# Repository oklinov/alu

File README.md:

View this project on [CADLAB.io](https://cadlab.io/project//TODO). 

# Template for PB170 projects at FI MU Brno
Add your user guide here.

## Photos

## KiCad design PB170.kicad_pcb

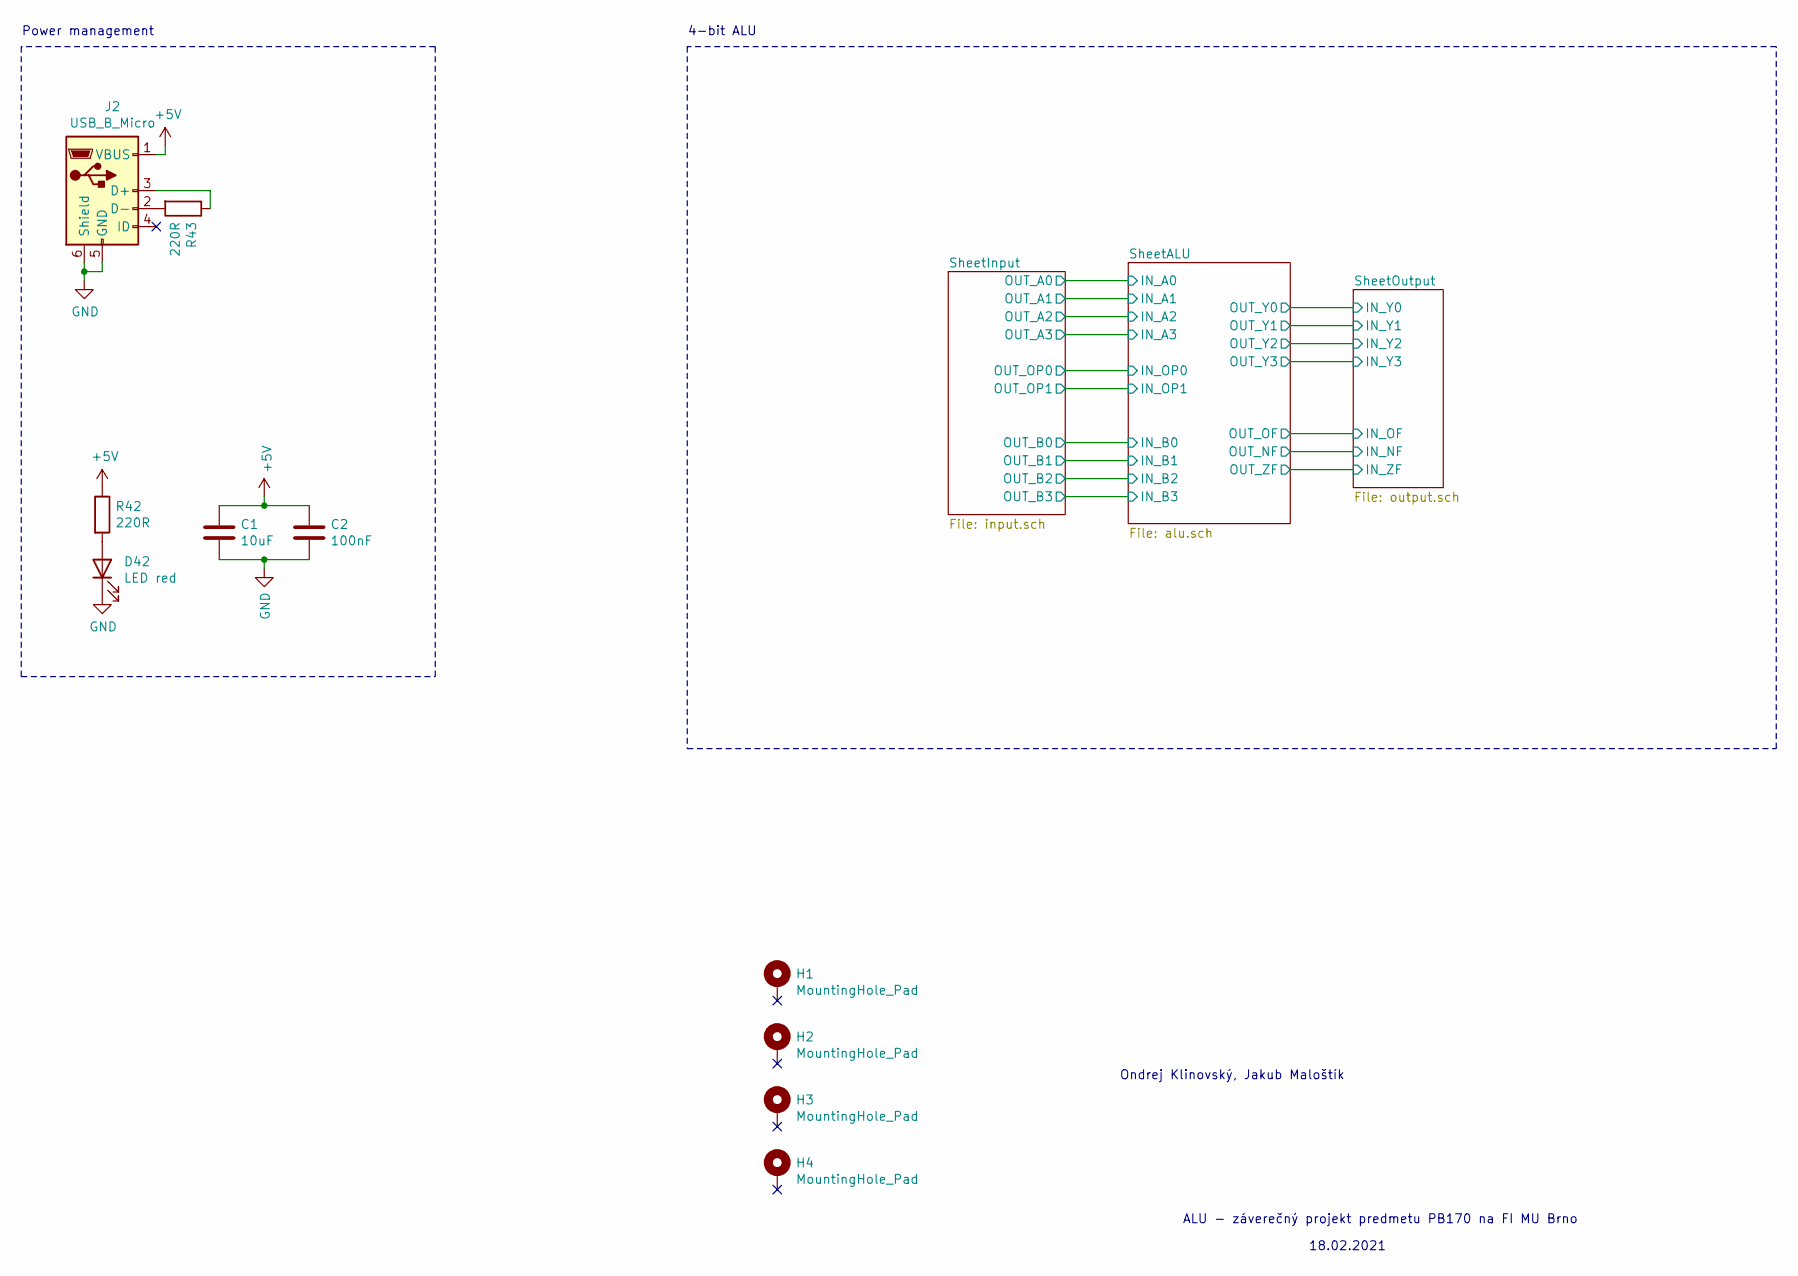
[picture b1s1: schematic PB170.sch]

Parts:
C1: 10uF; C_0805_2012Metric; LCSC C15850
C2: 100nF; C_0805_2012Metric; LCSC C14663
D42: LED red; LED_0603_1608Metric; LCSC C2286
H1, H2, H3, H4: MountingHole_Pad; MountingHole_3.2mm_M3_Pad
J2: USB_B_Micro; MICRO-USB-SMD_MICROXNJ; LCSC C404969
R42, R43: 220R; R_0603_1608Metric; LCSC C22962

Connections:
+5V: C1.1, C2.1, J2.1 (VBUS), R42.1; also elsewhere on the board
GND: C1.2, C2.2, D42.1 (K), J2.5 (GND), J2.6 (Shield); also elsewhere on the board
unnamed: D42.2 (A), R42.2
unnamed: J2.2 (D-), R43.2
unnamed: J2.3 (D+), R43.1

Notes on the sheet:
ALU - záverečný projekt predmetu PB170 na FI MU Brno
Ondrej Klinovský, Jakub Maloštík
Power management
4-bit ALU
18.02.2021

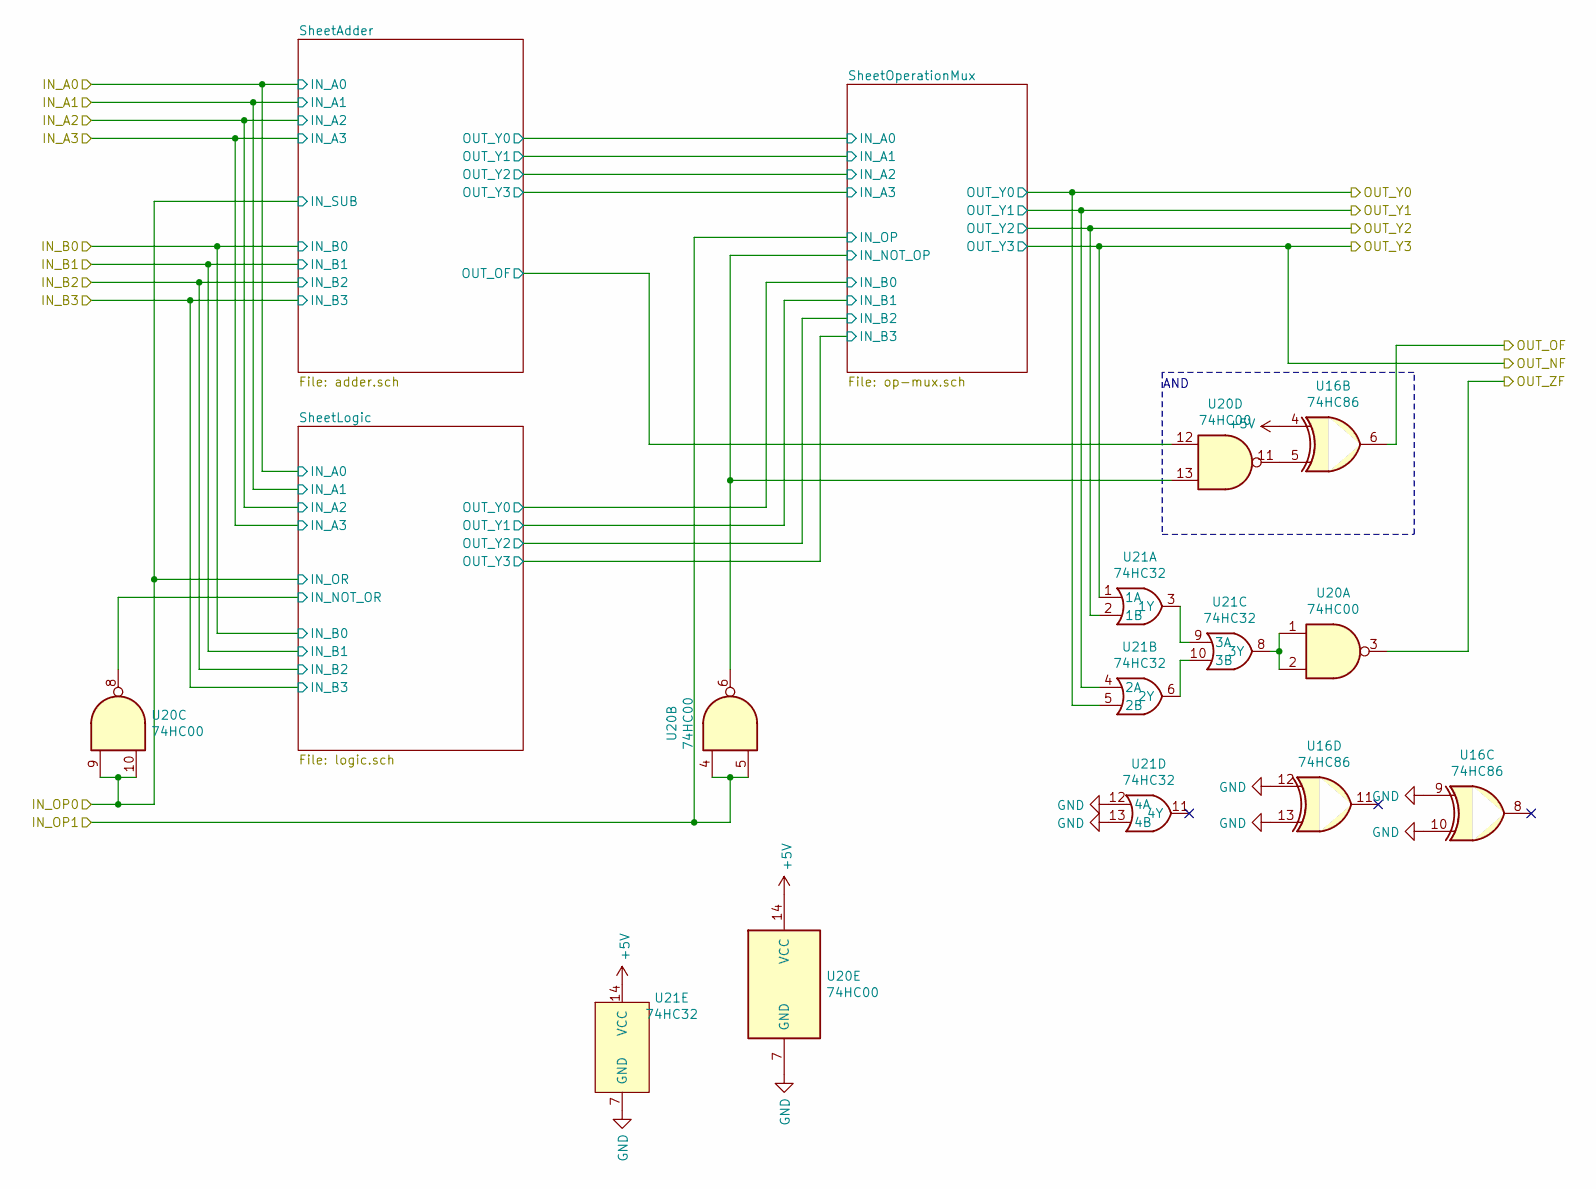
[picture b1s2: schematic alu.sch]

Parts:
U16: 74HC86; TSSOP-14_4.4x5mm_P0.65mm; LCSC C117522
U20: 74HC00; TSSOP-14_4.4x5mm_P0.65mm; LCSC C6807
U21: 74HC32; SOIC-14_3.9x8.7mm_P1.27mm; LCSC C5632

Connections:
+5V: U16.4, U20.14 (VCC), U21.14 (VCC); also elsewhere on the board
/SheetALU/IN_OP0: U20.9, U20.10; also elsewhere on the board
/SheetALU/IN_OP1: U20.4, U20.5; also elsewhere on the board
/SheetALU/SheetAdder/OUT_OF: U20.12; also elsewhere on the board
/SheetALU/SheetLogic/IN_NOT_OR: U20.8; also elsewhere on the board
/SheetALU/SheetOperationMux/IN_NOT_OP: U20.6, U20.13; also elsewhere on the board
/SheetOutput/IN_NF: U21.1 (1A); also elsewhere on the board
/SheetOutput/IN_OF: U16.6; also elsewhere on the board
/SheetOutput/IN_Y0: U21.5 (2B); also elsewhere on the board
/SheetOutput/IN_Y1: U21.4 (2A); also elsewhere on the board
/SheetOutput/IN_Y2: U21.2 (1B); also elsewhere on the board
/SheetOutput/IN_ZF: U20.3; also elsewhere on the board
GND: U16.9, U16.10, U16.12, U16.13, U20.7 (GND), U21.7 (GND), U21.12 (4A), U21.13 (4B); also elsewhere on the board
unnamed: U16.5, U20.11
unnamed: U20.1, U20.2, U21.8 (3Y)
unnamed: U21.3 (1Y), U21.9 (3A)
unnamed: U21.6 (2Y), U21.10 (3B)

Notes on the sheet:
AND

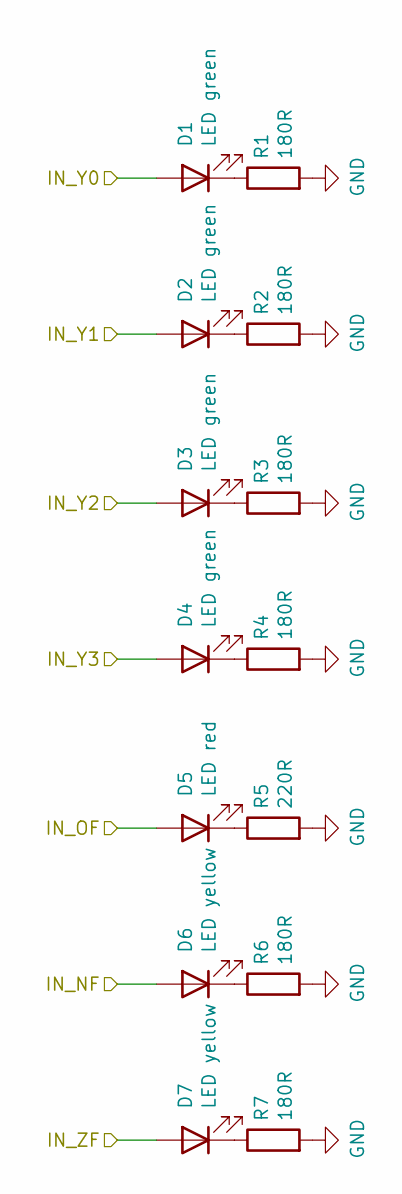
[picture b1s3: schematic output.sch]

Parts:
D1, D2, D3, D4: LED green; LED_0603_1608Metric; LCSC C72043
D5: LED red; LED_0603_1608Metric; LCSC C2286
D6, D7: LED yellow; LED_0603_1608Metric; LCSC C72038
R1, R2, R3, R4, R6, R7: 180R; R_0603_1608Metric; LCSC C22828
R5: 220R; R_0603_1608Metric; LCSC C22962

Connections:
/SheetOutput/IN_NF: D4.2 (A), D6.2 (A); also elsewhere on the board
/SheetOutput/IN_OF: D5.2 (A); also elsewhere on the board
/SheetOutput/IN_Y0: D1.2 (A); also elsewhere on the board
/SheetOutput/IN_Y1: D2.2 (A); also elsewhere on the board
/SheetOutput/IN_Y2: D3.2 (A); also elsewhere on the board
/SheetOutput/IN_ZF: D7.2 (A); also elsewhere on the board
GND: R1.2, R2.2, R3.2, R4.2, R5.2, R6.2, R7.2; also elsewhere on the board
unnamed: D1.1 (K), R1.1
unnamed: D2.1 (K), R2.1
unnamed: D3.1 (K), R3.1
unnamed: D4.1 (K), R4.1
unnamed: D5.1 (K), R5.1
unnamed: D6.1 (K), R6.1
unnamed: D7.1 (K), R7.1

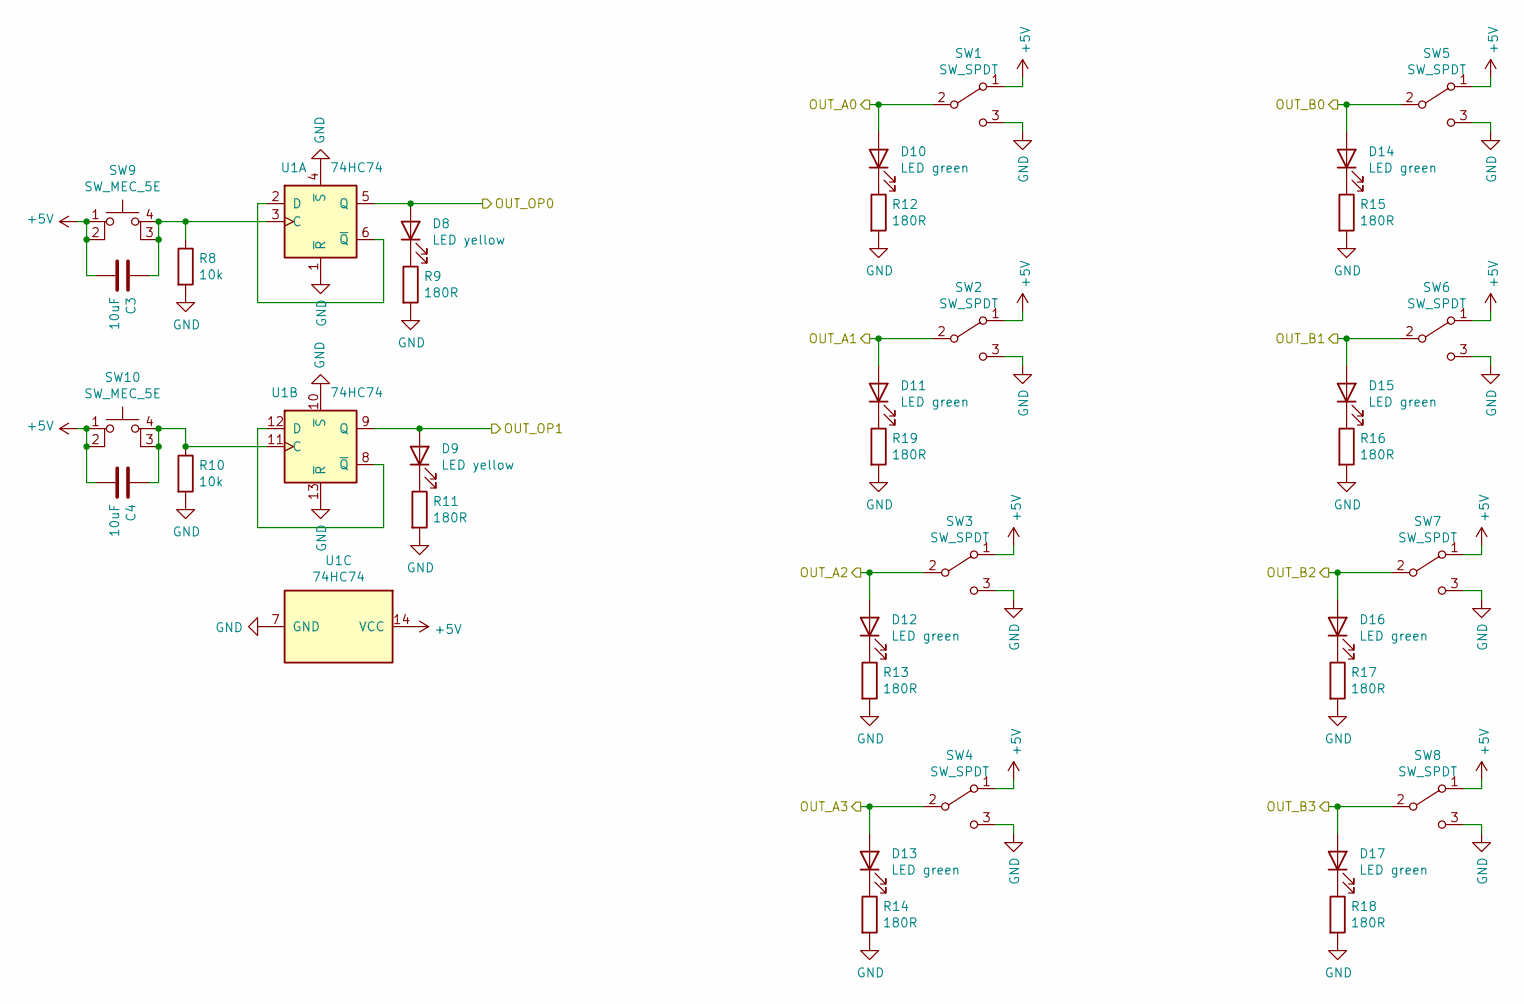
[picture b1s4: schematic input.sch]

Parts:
C3, C4: 10uF; C_0805_2012Metric; LCSC C15850
D8, D9: LED yellow; LED_0603_1608Metric; LCSC C72038
D10, D11, D12, D13, D14, D15, D16, D17: LED green; LED_0603_1608Metric; LCSC C72043
R8, R10: 10k; R_0603_1608Metric; LCSC C25804
R9, R11, R12, R13, R14, R15, R16, R17, R18, R19: 180R; R_0603_1608Metric; LCSC C22828
SW1, SW2, SW3, SW4, SW5, SW6, SW7, SW8: SW_SPDT; toggleSwitch; LCSC C136718
SW9, SW10: SW_MEC_5E; TactileSwitch_C381064; LCSC C381064
U1: 74HC74; TSSOP-14_4.4x5mm_P0.65mm; LCSC C6761

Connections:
+5V: C3.2, C4.2, SW1.1 (A), SW2.1 (A), SW3.1 (A), SW4.1 (A), SW5.1 (A), SW6.1 (A), SW7.1 (A), SW8.1 (A), SW9.1, SW9.2, SW10.1, SW10.2, U1.14 (VCC); also elsewhere on the board
/SheetALU/IN_A0: D10.2 (A), SW1.2 (B); also elsewhere on the board
/SheetALU/IN_A1: D11.2 (A), SW2.2 (B); also elsewhere on the board
/SheetALU/IN_A2: D12.2 (A), SW3.2 (B); also elsewhere on the board
/SheetALU/IN_A3: D13.2 (A), SW4.2 (B); also elsewhere on the board
/SheetALU/IN_B0: D14.2 (A), SW5.2 (B); also elsewhere on the board
/SheetALU/IN_B1: D15.2 (A), SW6.2 (B); also elsewhere on the board
/SheetALU/IN_B2: D16.2 (A), SW7.2 (B); also elsewhere on the board
/SheetALU/IN_B3: D17.2 (A), SW8.2 (B); also elsewhere on the board
/SheetALU/IN_OP0: D8.2 (A), U1.5 (Q); also elsewhere on the board
/SheetALU/IN_OP1: D9.2 (A), U1.9 (Q); also elsewhere on the board
GND: R8.2, R9.2, R10.2, R11.2, R12.2, R13.2, R14.2, R15.2, R16.2, R17.2, R18.2, R19.2, SW1.3 (C), SW2.3 (C), SW3.3 (C), SW4.3 (C), SW5.3 (C), SW6.3 (C), SW7.3 (C), SW8.3 (C), U1.1 (~R), U1.4 (~S), U1.7 (GND), U1.10 (~S), U1.13 (~R); also elsewhere on the board
unnamed: C3.1, R8.1, SW9.3 (K), SW9.4 (A), U1.3 (C)
unnamed: C4.1, R10.1, SW10.3 (K), SW10.4 (A), U1.11 (C)
unnamed: D8.1 (K), R9.1
unnamed: D9.1 (K), R11.1
unnamed: D10.1 (K), R12.1
unnamed: D11.1 (K), R19.1
unnamed: D12.1 (K), R13.1
unnamed: D13.1 (K), R14.1
unnamed: D14.1 (K), R15.1
unnamed: D15.1 (K), R16.1
unnamed: D16.1 (K), R17.1
unnamed: D17.1 (K), R18.1
unnamed: U1.2 (D), U1.6 (~Q)
unnamed: U1.8 (~Q), U1.12 (D)

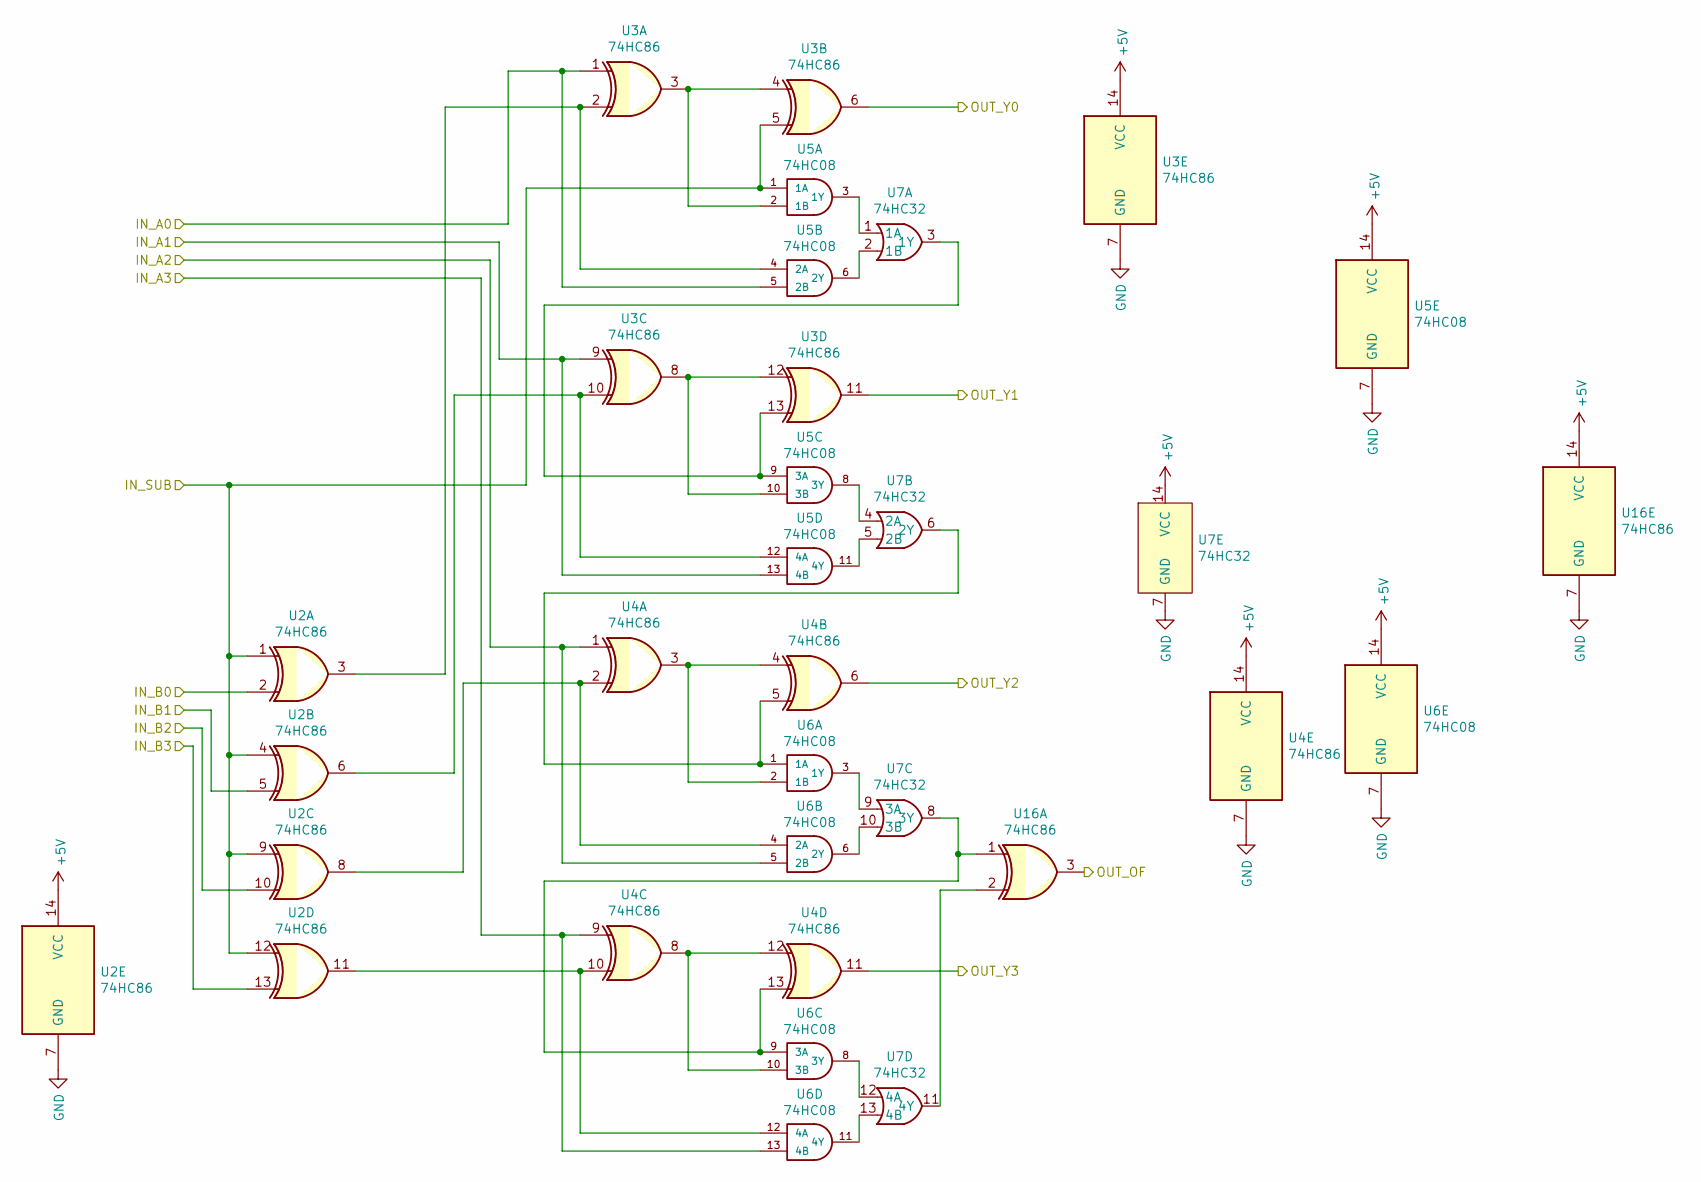
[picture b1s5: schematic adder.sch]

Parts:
U2, U3, U4, U16: 74HC86; TSSOP-14_4.4x5mm_P0.65mm; LCSC C117522
U5, U6: 74HC08; SOIC-14_3.9x8.7mm_P1.27mm; LCSC C5593
U7: 74HC32; SOIC-14_3.9x8.7mm_P1.27mm; LCSC C5632

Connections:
+5V: U2.14 (VCC), U3.14 (VCC), U4.14 (VCC), U5.14 (VCC), U6.14 (VCC), U7.14 (VCC), U16.14 (VCC); also elsewhere on the board
/SheetALU/IN_A0: U3.1, U5.5 (2B); also elsewhere on the board
/SheetALU/IN_A1: U3.9, U5.13 (4B); also elsewhere on the board
/SheetALU/IN_A2: U4.1, U6.5 (2B); also elsewhere on the board
/SheetALU/IN_A3: U4.9, U6.13 (4B); also elsewhere on the board
/SheetALU/IN_B0: U2.2; also elsewhere on the board
/SheetALU/IN_B1: U2.5; also elsewhere on the board
/SheetALU/IN_B2: U2.10; also elsewhere on the board
/SheetALU/IN_B3: U2.13; also elsewhere on the board
/SheetALU/IN_OP0: U2.1, U2.4, U2.9, U2.12, U3.5, U5.1 (1A); also elsewhere on the board
/SheetALU/SheetAdder/OUT_OF: U16.3; also elsewhere on the board
/SheetALU/SheetOperationMux/IN_A0: U3.6; also elsewhere on the board
/SheetALU/SheetOperationMux/IN_A1: U3.11; also elsewhere on the board
/SheetALU/SheetOperationMux/IN_A2: U4.6; also elsewhere on the board
/SheetALU/SheetOperationMux/IN_A3: U4.11; also elsewhere on the board
GND: U2.7 (GND), U3.7 (GND), U4.7 (GND), U5.7 (GND), U6.7 (GND), U7.7 (GND), U16.7 (GND); also elsewhere on the board
unnamed: U2.3, U3.2, U5.4 (2A)
unnamed: U2.6, U3.10, U5.12 (4A)
unnamed: U2.8, U4.2, U6.4 (2A)
unnamed: U2.11, U4.10, U6.12 (4A)
unnamed: U3.3, U3.4, U5.2 (1B)
unnamed: U3.8, U3.12, U5.10 (3B)
unnamed: U3.13, U5.9 (3A), U7.3 (1Y)
unnamed: U4.3, U4.4, U6.2 (1B)
unnamed: U4.5, U6.1 (1A), U7.6 (2Y)
unnamed: U4.8, U4.12, U6.10 (3B)
unnamed: U5.3 (1Y), U7.1 (1A)
unnamed: U5.6 (2Y), U7.2 (1B)
unnamed: U5.8 (3Y), U7.4 (2A)
unnamed: U5.11 (4Y), U7.5 (2B)
unnamed: U6.3 (1Y), U7.9 (3A)
unnamed: U6.6 (2Y), U7.10 (3B)
unnamed: U6.8 (3Y), U7.12 (4A)
unnamed: U6.11 (4Y), U7.13 (4B)
unnamed: U4.13, U6.9 (3A), U7.8 (3Y), U16.1
unnamed: U7.11 (4Y), U16.2

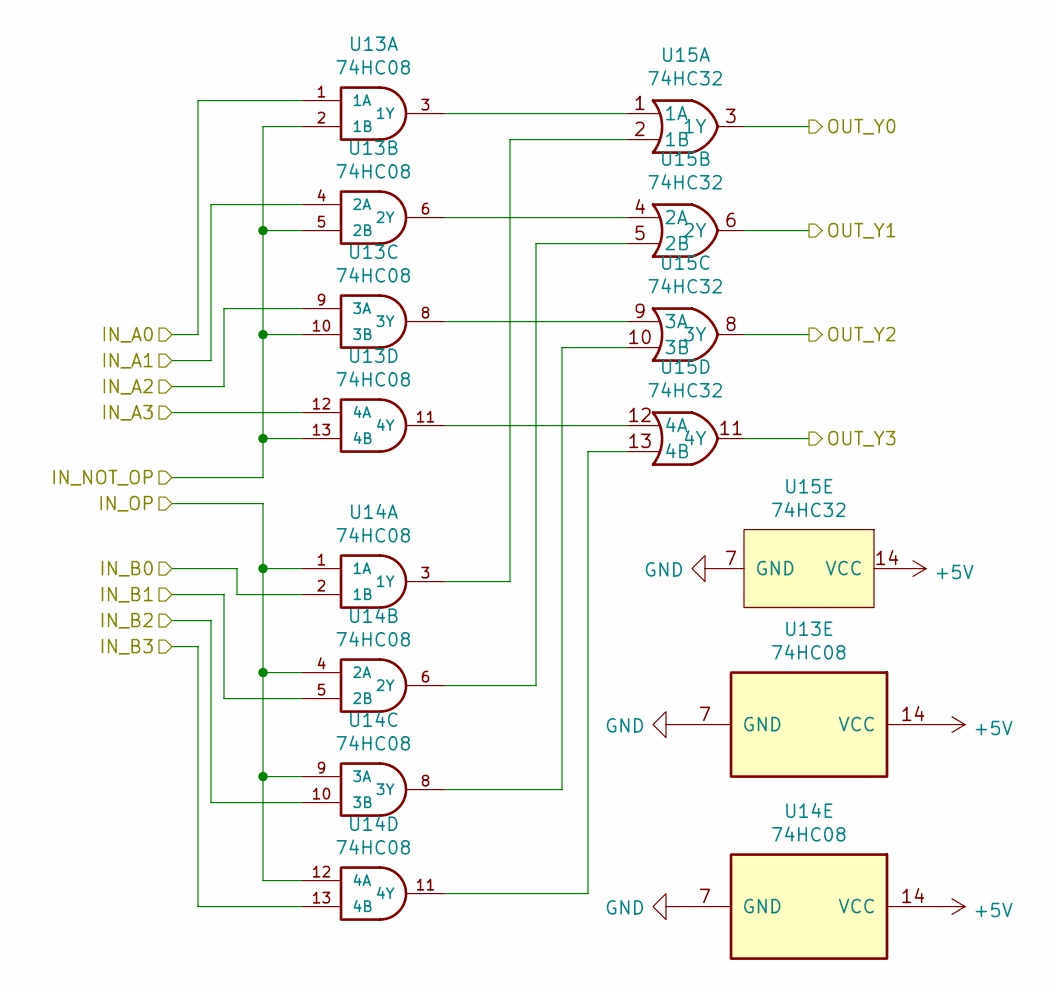
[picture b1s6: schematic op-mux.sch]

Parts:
U13, U14: 74HC08; SOIC-14_3.9x8.7mm_P1.27mm; LCSC C5593
U15: 74HC32; SOIC-14_3.9x8.7mm_P1.27mm; LCSC C5632

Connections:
+5V: U13.14 (VCC), U14.14 (VCC), U15.14 (VCC); also elsewhere on the board
/SheetALU/IN_OP1: U14.1 (1A), U14.4 (2A), U14.9 (3A), U14.12 (4A); also elsewhere on the board
/SheetALU/SheetOperationMux/IN_A0: U13.1 (1A); also elsewhere on the board
/SheetALU/SheetOperationMux/IN_A1: U13.4 (2A); also elsewhere on the board
/SheetALU/SheetOperationMux/IN_A2: U13.9 (3A); also elsewhere on the board
/SheetALU/SheetOperationMux/IN_A3: U13.12 (4A); also elsewhere on the board
/SheetALU/SheetOperationMux/IN_B0: U14.2 (1B); also elsewhere on the board
/SheetALU/SheetOperationMux/IN_B1: U14.5 (2B); also elsewhere on the board
/SheetALU/SheetOperationMux/IN_B2: U14.10 (3B); also elsewhere on the board
/SheetALU/SheetOperationMux/IN_B3: U14.13 (4B); also elsewhere on the board
/SheetALU/SheetOperationMux/IN_NOT_OP: U13.2 (1B), U13.5 (2B), U13.10 (3B), U13.13 (4B); also elsewhere on the board
/SheetOutput/IN_NF: U15.11 (4Y); also elsewhere on the board
/SheetOutput/IN_Y0: U15.3 (1Y); also elsewhere on the board
/SheetOutput/IN_Y1: U15.6 (2Y); also elsewhere on the board
/SheetOutput/IN_Y2: U15.8 (3Y); also elsewhere on the board
GND: U13.7 (GND), U14.7 (GND), U15.7 (GND); also elsewhere on the board
unnamed: U13.3 (1Y), U15.1 (1A)
unnamed: U13.6 (2Y), U15.4 (2A)
unnamed: U13.8 (3Y), U15.9 (3A)
unnamed: U13.11 (4Y), U15.12 (4A)
unnamed: U14.3 (1Y), U15.2 (1B)
unnamed: U14.6 (2Y), U15.5 (2B)
unnamed: U14.8 (3Y), U15.10 (3B)
unnamed: U14.11 (4Y), U15.13 (4B)

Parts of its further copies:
U10, U11: 74HC08; SOIC-14_3.9x8.7mm_P1.27mm; LCSC C5593
U12: 74HC32; SOIC-14_3.9x8.7mm_P1.27mm; LCSC C5632

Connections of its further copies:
+5V: U10.14 (VCC), U11.14 (VCC), U12.14 (VCC); also elsewhere on the board
/SheetALU/IN_OP0: U11.1 (1A), U11.4 (2A), U11.9 (3A), U11.12 (4A); also elsewhere on the board
/SheetALU/SheetLogic/IN_NOT_OR: U10.2 (1B), U10.5 (2B), U10.10 (3B), U10.13 (4B); also elsewhere on the board
/SheetALU/SheetLogic/sheet6027A5E8/IN_A0: U10.1 (1A); also elsewhere on the board
/SheetALU/SheetLogic/sheet6027A5E8/IN_A1: U10.4 (2A); also elsewhere on the board
/SheetALU/SheetLogic/sheet6027A5E8/IN_A2: U10.9 (3A); also elsewhere on the board
/SheetALU/SheetLogic/sheet6027A5E8/IN_A3: U10.12 (4A); also elsewhere on the board
/SheetALU/SheetLogic/sheet6027A5E8/IN_B0: U11.2 (1B); also elsewhere on the board
/SheetALU/SheetLogic/sheet6027A5E8/IN_B1: U11.5 (2B); also elsewhere on the board
/SheetALU/SheetLogic/sheet6027A5E8/IN_B2: U11.10 (3B); also elsewhere on the board
/SheetALU/SheetLogic/sheet6027A5E8/IN_B3: U11.13 (4B); also elsewhere on the board
/SheetALU/SheetOperationMux/IN_B0: U12.3 (1Y); also elsewhere on the board
/SheetALU/SheetOperationMux/IN_B1: U12.6 (2Y); also elsewhere on the board
/SheetALU/SheetOperationMux/IN_B2: U12.8 (3Y); also elsewhere on the board
/SheetALU/SheetOperationMux/IN_B3: U12.11 (4Y); also elsewhere on the board
GND: U10.7 (GND), U11.7 (GND), U12.7 (GND); also elsewhere on the board
unnamed: U10.3 (1Y), U12.1 (1A)
unnamed: U10.6 (2Y), U12.4 (2A)
unnamed: U10.8 (3Y), U12.9 (3A)
unnamed: U10.11 (4Y), U12.12 (4A)
unnamed: U11.3 (1Y), U12.2 (1B)
unnamed: U11.6 (2Y), U12.5 (2B)
unnamed: U11.8 (3Y), U12.10 (3B)
unnamed: U11.11 (4Y), U12.13 (4B)

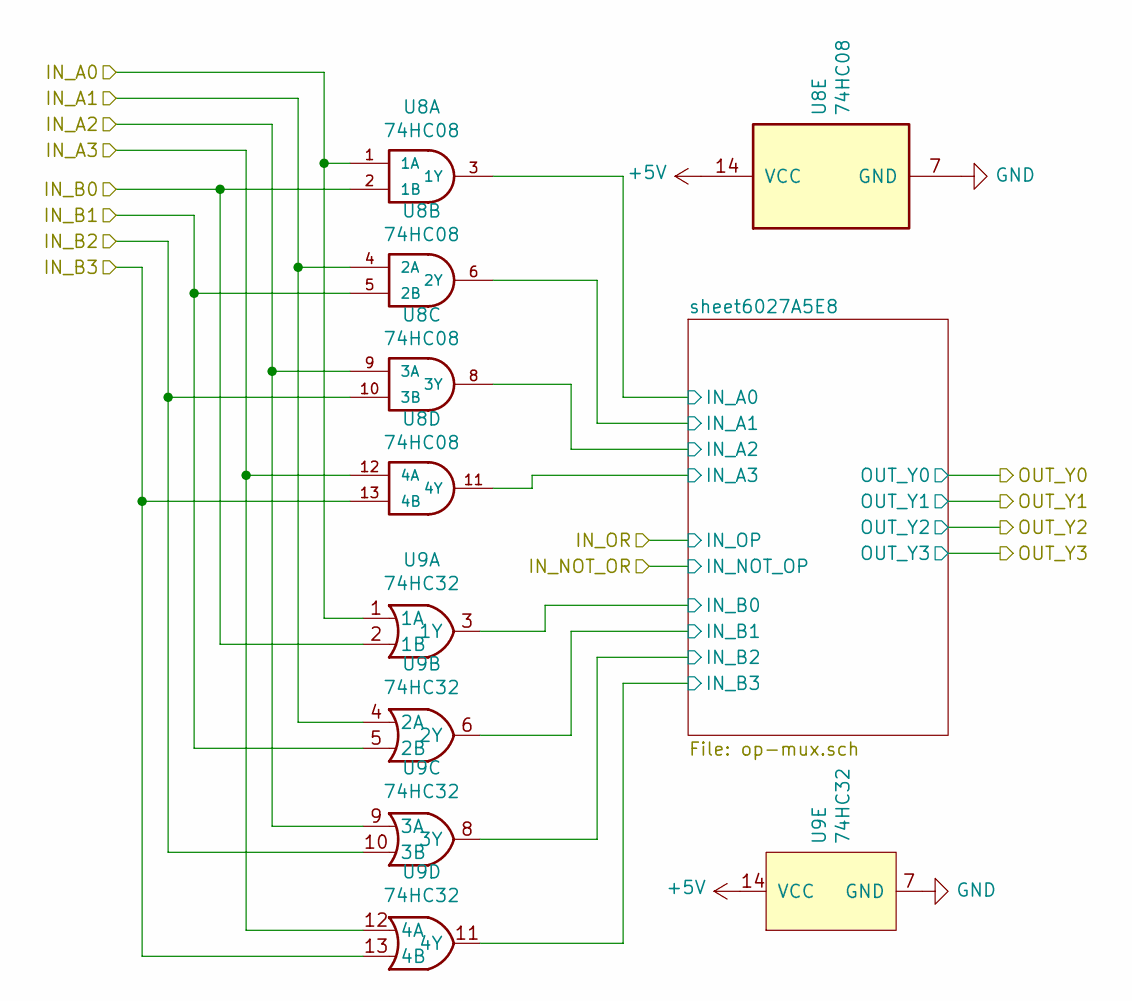
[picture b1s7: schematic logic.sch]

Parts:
U8: 74HC08; SOIC-14_3.9x8.7mm_P1.27mm; LCSC C5593
U9: 74HC32; SOIC-14_3.9x8.7mm_P1.27mm; LCSC C5632

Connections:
+5V: U8.14 (VCC), U9.14 (VCC); also elsewhere on the board
/SheetALU/IN_A0: U8.1 (1A), U9.1 (1A); also elsewhere on the board
/SheetALU/IN_A1: U8.4 (2A), U9.4 (2A); also elsewhere on the board
/SheetALU/IN_A2: U8.9 (3A), U9.9 (3A); also elsewhere on the board
/SheetALU/IN_A3: U8.12 (4A), U9.12 (4A); also elsewhere on the board
/SheetALU/IN_B0: U8.2 (1B), U9.2 (1B); also elsewhere on the board
/SheetALU/IN_B1: U8.5 (2B), U9.5 (2B); also elsewhere on the board
/SheetALU/IN_B2: U8.10 (3B), U9.10 (3B); also elsewhere on the board
/SheetALU/IN_B3: U8.13 (4B), U9.13 (4B); also elsewhere on the board
/SheetALU/SheetLogic/sheet6027A5E8/IN_A0: U8.3 (1Y); also elsewhere on the board
/SheetALU/SheetLogic/sheet6027A5E8/IN_A1: U8.6 (2Y); also elsewhere on the board
/SheetALU/SheetLogic/sheet6027A5E8/IN_A2: U8.8 (3Y); also elsewhere on the board
/SheetALU/SheetLogic/sheet6027A5E8/IN_A3: U8.11 (4Y); also elsewhere on the board
/SheetALU/SheetLogic/sheet6027A5E8/IN_B0: U9.3 (1Y); also elsewhere on the board
/SheetALU/SheetLogic/sheet6027A5E8/IN_B1: U9.6 (2Y); also elsewhere on the board
/SheetALU/SheetLogic/sheet6027A5E8/IN_B2: U9.8 (3Y); also elsewhere on the board
/SheetALU/SheetLogic/sheet6027A5E8/IN_B3: U9.11 (4Y); also elsewhere on the board
GND: U8.7 (GND), U9.7 (GND); also elsewhere on the board

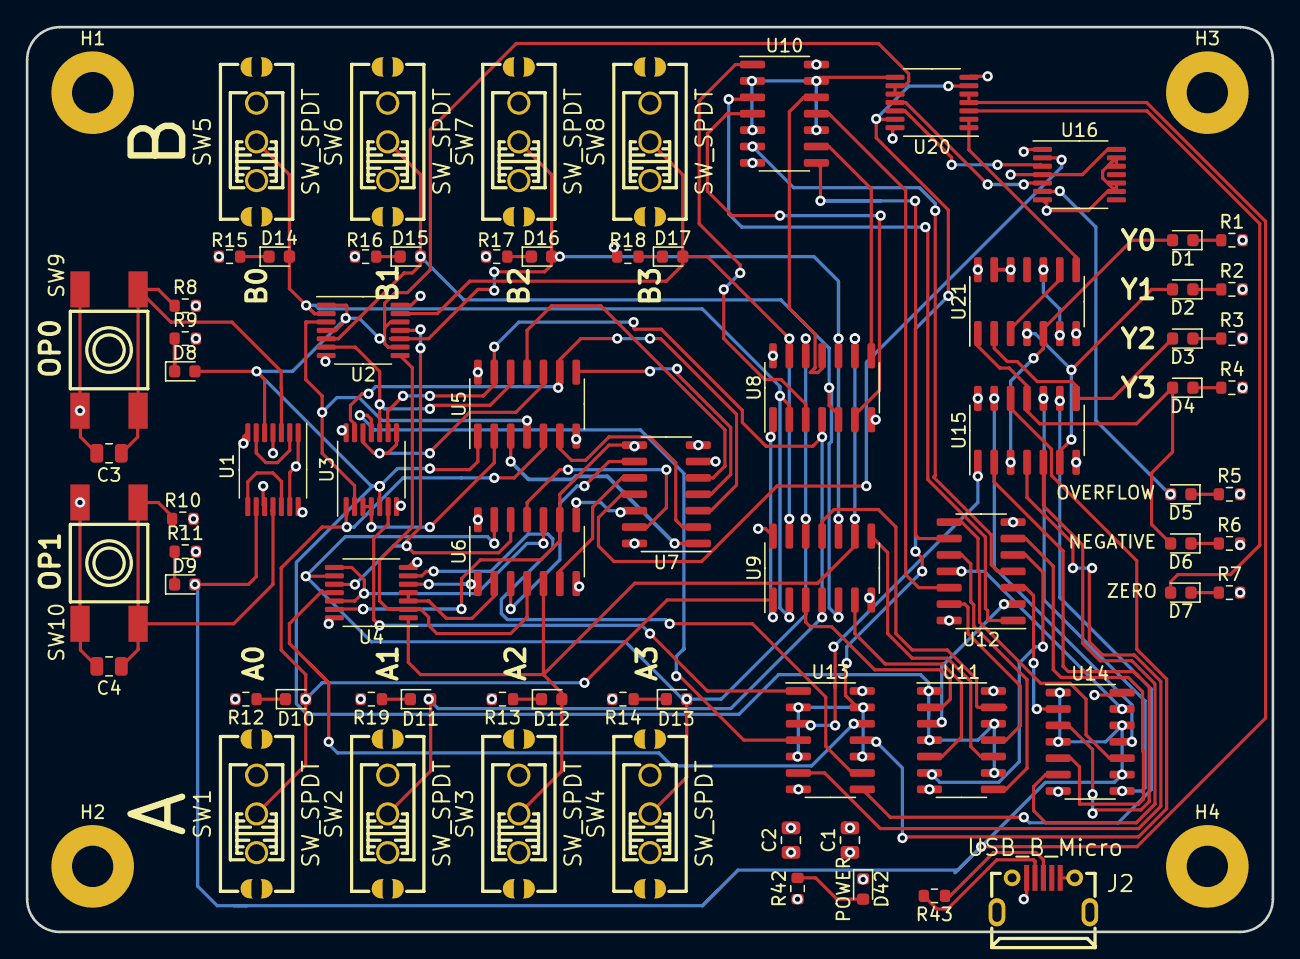
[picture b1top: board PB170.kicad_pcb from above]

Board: 4 copper layers, 96.5 x 70.1 mm, 76 parts (0 on the bottom side), 101 nets.

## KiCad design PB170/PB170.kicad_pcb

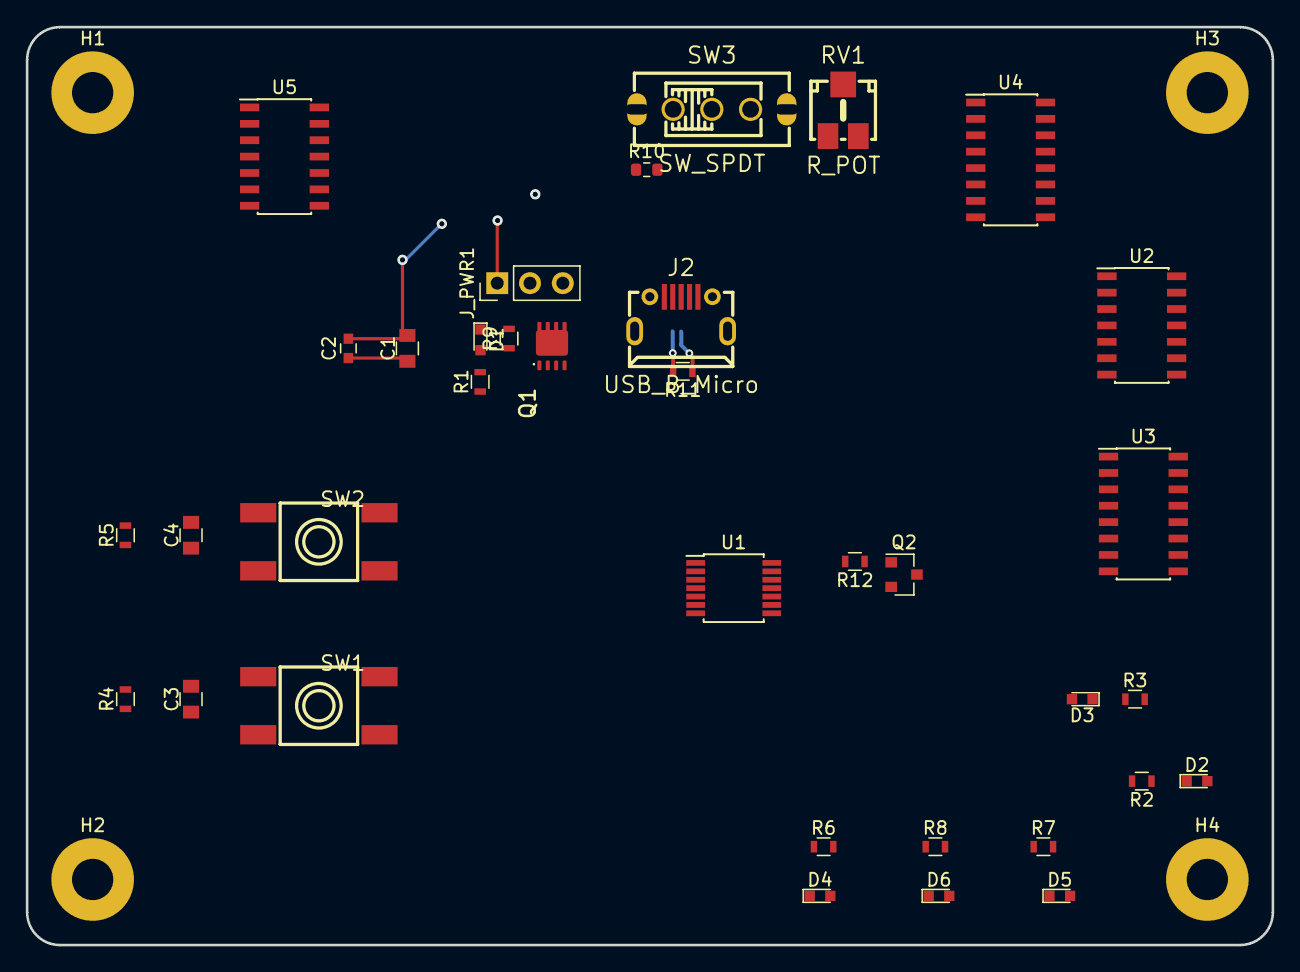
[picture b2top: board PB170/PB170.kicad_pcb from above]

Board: 4 copper layers, 96.5 x 71.1 mm, 39 parts (0 on the bottom side), 21 nets.

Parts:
C1, C3, C4: 10uF; C_0805
C2: 100nF; C_0603
D1: LED red; LED_0603
D2, D3: LED yellow; LED_0603
D4: LED green; LED_0603
D5: LED blue; LED_0603
D6: LED white; LED_0603
H1, H2, H3, H4: MountingHole_Pad; MountingHole_3.2mm_M3_Pad
J2: USB_B_Micro; MICRO-USB-SMD_MICROXNJ
J_PWR1: Conn_01x03; Pin_Header_Straight_1x03_Pitch2.54mm
Q1: P-MOSFET-MLP_HS; MLP3.3X3.3_HS
Q2: BC817; SOT-23
R1, R7, R11, R12: 220R; R_0603
R2, R3, R6: 180R; R_0603
R4, R5, R9: 10k; R_0603
R8: 130R; R_0603
R10: 10k; R_0603_1608Metric
RV1: R_POT; potentiometer10k
SW1, SW2: SW_MEC_5E; TactileSwitch_C381064
SW3: SW_SPDT; toggleSwitch
U1: 74HC00; TSSOP-14_4.4x5mm_Pitch0.65mm
U2: 74HC08; SOIC-14_3.9x8.7mm_Pitch1.27mm
U3: 74HC4511D; SOIC-16_3.9x9.9mm_Pitch1.27mm
U4: HEF4518BT; SOIC-16_3.9x9.9mm_Pitch1.27mm
U5: 74HC32; SOIC-14_3.9x8.7mm_Pitch1.27mm

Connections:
+5V: C1.1, C2.1, C3.2, C4.2, J2.1, Q1.1, Q1.2, Q1.3, Q2.3, R1.1, RV1.1, SW1.1, SW1.2, SW2.1, SW2.2, SW3.1, U1.14, U2.14, U3.16, U4.16, U5.14
/SheetXOR/IN_A: C3.1, D2.2, R4.1, SW1.3, SW1.4, U1.1, U1.4
/SheetXOR/IN_B: C4.1, D3.2, R5.1, SW2.3, SW2.4, U1.2, U1.10
GND: C1.2, C2.2, D1.1, J2.5, J2.6, J_PWR1.1, J_PWR1.3, R2.2, R3.2, R4.2, R5.2, R6.2, R7.2, R8.2, R9.2, R10.2, SW3.3, U1.7, U2.7, U3.8, U4.8, U5.7
unnamed: D1.2, R1.2
unnamed: D2.1, R2.1
unnamed: D3.1, R3.1
unnamed: D4.1, R6.1
unnamed: D4.2, D5.2, D6.2, Q2.2
unnamed: D5.1, R7.1
unnamed: D6.1, R8.1
unnamed: J2.2, R11.2
unnamed: J2.3, R11.1
unnamed: J_PWR1.2, Q1.5, Q1.6, Q1.7, Q1.8, Q1.9
unnamed: Q1.4, R9.1
unnamed: Q2.1, R12.1
unnamed: R10.1, RV1.3
unnamed: U1.3, U1.5, U1.9
unnamed: U1.6, U1.12
unnamed: U1.8, U1.13
OUTPUT: R12.2, U1.11

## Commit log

2020-12-08 Initial commit.
2020-12-09 Added PCB.
2020-12-09 Added hierarchical sheet example.
2020-12-10 Added 3D packages.
2020-12-27 Experimentally added 74HC08 symbol.
2020-12-27 Added 74HC4511D and HEF4518BT.
2021-01-15 Added sample OR gate 74HC32.
2021-01-21 Setup xor component, create ALU and ADDER sheets
2021-01-21 Create adder
2021-01-23 Create sheet for logic part
2021-01-23 Create operation multiplexer
2021-01-23 Create overlow label in adder
2021-01-23 Add alu output flags
2021-01-23 Create empty InputSheet and OutputSheet
2021-01-27 ALU finished
2021-02-02 Remove xor from the main sheet
2021-02-05 Added THT parts.
2021-02-05 Created examples with new THT parts.
2021-02-05 added switching buttons
2021-02-07 Fixed 3D packages.
2021-02-07 Added sample previews.
2021-02-07 Added photos to README.md
2021-02-07 Fixed README.md
2021-02-07 Fixed ovelapping parts.
2021-02-07 Moved KiCad content from PB170 to root folder.
2021-02-09 Changes kicad did when launching after merge
2021-02-09 Add missing wire in adder
2021-02-09 Add input switches
2021-02-09 Annotate components in input and output
2021-02-09 Anotate alu
2021-02-10 tiny fixes in annotation
2021-02-10 exchanged a single AND
2021-02-10 removed USB C connector
2021-02-11 minor fixes
2021-02-11 fixed some footprints
2021-02-12 Change R, C and LED footprints
2021-02-14 Put components on board, set up 3d models of button and switch
2021-02-14 Add documentation draft
2021-02-15 Čiarka
2021-02-16 Finished routing
2021-02-17 Added labels
2021-02-18 Create poster
2021-02-18 Fill main sheet header
2021-02-18 Restore simulation file
2021-02-18 Update simulation file
2021-02-18 Remove tmp file
2021-02-18 Signature
2021-02-18 Final touches
2021-02-19 Add doc images
2021-02-19 Add pdfs
2021-02-20 Prettify simulation
2021-02-20 Add sheet screenshots to doc (todo: add caption)
2021-02-20 Add caption
2021-02-20 Update poster
2021-02-20 Fix arrow in poster
2021-02-20 Add captions
2021-02-20 Set image width to .8/linewidth
2021-02-20 Put text before images
2021-02-20 Minor changes
